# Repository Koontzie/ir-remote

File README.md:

# IR-Remote

**A three-button universal IR remote you program from your phone** — an ESP32-S3
blasts the infrared code, and a web page (no app store, no build step) tells it
which code to blast over Bluetooth.

The point is the last-mile problem in AV work: you're standing in front of an
unlabelled projector or a hotel TV with no remote, and you need power and input
switching *now*. This is a Flipper Zero's universal-remote trick, on $10 of parts,
in a form factor with real buttons you can hit without looking.

## Try it

**→ [koontzie.github.io/ir-remote/app/](https://koontzie.github.io/ir-remote/app/)**

The app is a single static HTML file with no dependencies and no backend. It talks
to the board with **Web Bluetooth**, which means:

- **Desktop Chrome / Edge / Android Chrome** — works as-is.
- **iOS: you need [Bluefy](https://apps.apple.com/us/app/bluefy-web-ble-browser/id1492822055).**
  Not a preference — **Safari has no Web Bluetooth support at all**, and every iOS
  browser is Safari underneath except the handful that ship their own BLE bridge.
  Bluefy is one of those. Open the link above inside Bluefy.
- **Firefox** — no Web Bluetooth. Won't work.

Without hardware you can still browse the code library; the connect button is the
only thing that needs a board.

## How it works

```
[phone or laptop browser]  ──Web Bluetooth──▶  [ESP32-S3 · BLE GATT]
                                                     │  writes to NVS (flash)
[3 physical buttons] ──GPIO──▶ [firmware] ──▶ [2N2222 ──▶ 2× IR LED] ──▶ device
```

Assign a code to a slot once, and the board **keeps it through a power cycle and
fires it with the browser completely disconnected.** It's a real remote, not a
Bluetooth accessory — the phone is a programming tool, not a dependency.

The code library ships in the repo: **317 brands, ~11,100 codes** across TVs,
projectors, monitors, AV receivers, soundbars, cable boxes, Blu-ray and DVD.
Search a brand, pick a function, assign it to a button. Codes shared across many
models of a brand are flagged as "blanket" codes and floated to the top, because
those are the ones most likely to just work.

**GATT interface** (device name `IR-Remote`):

| Role | UUID | Payload |
|---|---|---|
| service | `b457c32b-22b1-425f-8a88-4d6dc37ba4eb` | — |
| `config` (write) | `d997012d-7d2b-47de-ae87-bae14df446ef` | `{"slot":1,"proto":"SAMSUNG","code":"0xE0E040BF","bits":32}` |
| `trigger` (write) | `58397514-04a3-4265-9590-9d910c4e99d2` | `{"slot":1}` |
| `status` (notify) | `b8ddfe01-519f-430d-bd4e-aba0dd852e2c` | `saved:N` / `sent:N` / `pressed:N` / `err:…` |

Five slots (1–5); protocols NEC, SAMSUNG, SONY.

⚠️ **The GATT server is unauthenticated** — anyone in Bluetooth range can write a
config or trigger a slot. That's fine for bench use and it's a deliberate
trade-off, not an oversight; NimBLE bonding would close it if this ever left the
workbench.

## Where it stands

**It works.** The core is built and proven on the bench: IR transmit across a room
(20–30 ft), programming over Bluetooth from the app, codes persisting in flash
through a power cycle, all three physical buttons, and the searchable code library
end to end — pick a Samsung power code in the browser, assign it to a button, and
the TV across the room turns off.

It's a finished thing that does its job. What follows is the honest edge of it,
not a to-do list I'm apologising for.

- **USB-powered.** The circuit runs off the dev board's 5 V pin, so it needs a
  cable or a USB battery pack. A battery-and-deep-sleep version was started and
  stopped after it cost a dev board — see the postmortem below.
- **Identify mode is written but unproven.** Sweeping power codes until the device
  reacts, plus favourites, is implemented in the app and firmware but has never
  been run against real hardware.
- **The custom PCB is designed, not fabricated.** `hardware/` has a complete
  KiCad project, placed and partly routed. Nothing has been sent to a fab, so
  nothing about it is proven.
- **Bluetooth link drops occasionally** (`reason 520`, supervision timeout).
  Annoying, not dangerous — the stored codes and the IR output were verified
  correct either side of every drop.

The unit in the photos is currently dead, and it's a good story rather than a sad
one: during the battery experiment a cheap boost converter's solder-blob voltage
selector let go, silently jumped to 9 V, and cooked the dev board's regulator. The
design was never at fault, a socketed dev board makes it a two-minute swap, and
the full postmortem — along with every other fault this project hit — is in
[docs/DEVLOG.md](docs/DEVLOG.md).

## What's next

No timeline and no promises — the project does what it was built to do. If I pick
it back up:

- **An enclosure.** It's loose boards and panel-mount buttons right now. This is
  the one thing that would turn it from a working circuit into something you'd
  actually carry to a job.
- **Prove out identify mode** on a fresh dev board — the sweep is the feature that
  makes it genuinely universal rather than a nice code browser.
- **Polish the app UI.** It's functional and fast, but it's plainly a tool built
  by one person for one person.

## Bill of materials

| Qty | Part | Notes |
|---|---|---|
| 1 | **Seeed Studio XIAO ESP32-S3** dev board | Any ESP32-S3 dev board works; this is what's pictured. **Socket it** — dev boards die, and a socket makes that a pull instead of a desolder. |
| 2 | IR LED, 940 nm | Wired in series. Salvaged from a dead remote here. Verify a salvaged emitter is actually IR — it glows violet-white on a phone camera. |
| 1 | 2N2222 NPN transistor, TO-92 | Any general-purpose NPN with ≥150 mA collector current. |
| 1 | 33 Ω resistor | LED current limit — sets the ~100 mA pulse. |
| 1 | 1 kΩ resistor | Transistor base. |
| 1 | 470 µF electrolytic capacitor | Bulk decoupling across the 5 V rail. Steadies the rail during LED pulses. |
| 3 | R13-507 16 mm momentary buttons | Panel-mount, solder lugs, no polarity. Any momentary SPST works. |
| 1 | Protoboard + hookup wire | |

Roughly $10–15 if you're buying everything, less if you're raiding a parts bin.

## Wiring

Full card with health checks and measured values: **[hardware/WIRING.md](hardware/WIRING.md)**.

```
POWER
  Dev board 5V pin ──► 5V rail
  Dev board GND    ──► GND rail
  470µF cap across the rails: (+) → 5V, (−) stripe → GND, near the driver.

IR DRIVER (2N2222, TO-92)
  5V rail ──33Ω──► LED1 anode(+)
  LED1(−) ──► LED2(+)                 [series pair, both 940nm]
  LED2(−) ──► COLLECTOR
  EMITTER ──► GND rail
  GPIO4 ──1kΩ──► BASE (middle leg)

BUTTONS (INPUT_PULLUP, pressed = LOW)
  GPIO5 ──► button ──► GND   → slot 1
  GPIO2 ──► button ──► GND   → slot 2
  GPIO7 ──► button ──► GND   → slot 3
```

Two things that cost real bench time here, so they're worth repeating:

- **Meter the transistor's legs; don't assume them.** E/C order varies by vendor
  for the same part number. In diode mode with the red probe on Base, the outer
  leg with the *higher* forward drop is the Emitter.
- **A resistor being present on the board is not the same as it being in the
  current path.** The 33 Ω must be in series with the LEDs, not in the cap's
  branch. Check continuity to the right *node*.

## Build and flash

Toolchain (macOS, Homebrew) — these exact versions are what's verified:

| | Version |
|---|---|
| `arduino-cli` | 1.5.1 |
| `esp32` core | 3.3.10 |
| IRremoteESP8266 | 2.9.0 |
| NimBLE-Arduino | 2.5.0 |
| ArduinoJson | 7.4.3 |

```sh
arduino-cli core install esp32:esp32
arduino-cli lib install IRremoteESP8266 NimBLE-Arduino ArduinoJson

arduino-cli board list      # the port number is NOT stable across replugs
arduino-cli compile --fqbn esp32:esp32:esp32s3:CDCOnBoot=cdc firmware/remote_ble
arduino-cli upload -p <PORT> --fqbn esp32:esp32:esp32s3:CDCOnBoot=cdc firmware/remote_ble

sleep 20 | arduino-cli monitor -p <PORT> -c baudrate=115200
```

`CDCOnBoot=cdc` is required — the S3 talks over native USB CDC, and serial stays
silent without it. `arduino-cli monitor` exits instantly if stdin is closed, hence
the `sleep 20 |` when scripting it.

`firmware/phase1_ir_test/` is a deliberately minimal known-good IR sketch — it
sends one hard-coded Samsung code every 3 seconds. When something stops working,
flash that first to prove the LED path before suspecting anything else.

### Running the app locally

```sh
cd app && python3 -m http.server 8000
```

Open `http://localhost:8000` in desktop Chrome. `localhost` counts as a secure
context, so Web Bluetooth works without HTTPS.

## Repository layout

| Path | What |
|---|---|
| `firmware/remote_ble/` | The real firmware — BLE GATT + IR + 5 NVS-backed slots |
| `firmware/phase1_ir_test/` | Minimal known-good IR sketch, kept as a bisect tool |
| `app/index.html` | The whole app. One file, vanilla JS, no build step |
| `data/` | Generated IR code database — see [data/README.md](data/README.md) |
| `tools/flipper_ir_convert.py` | Flipper `.ir` → IRremoteESP8266 JSON converter + scraper |
| `hardware/` | KiCad 10 PCB project (unfabricated) + the wiring card |
| `docs/` | Design docs and the development log |
| `PLAN.md` | The plan |
| `docs/DEVLOG.md` | A running log of what actually happened — including the failures, in detail |

### Docs

[Code library + Identify mode design](docs/DESIGN-code-library.md) ·
[PCB design](hardware/DESIGN-pcb.md) ·
[hardware working notes](hardware/README.md) ·
[the IR database](data/README.md)

`docs/DEVLOG.md` is worth a look if you're building one of these. It's a blow-by-blow
of every fault hit along the way and how each was actually diagnosed — a dev board
bricked by a boost converter that silently drifted to 9 V, a transistor installed
E/C-reversed, a BLE advertisement overflowing 31 bytes so the device name was
silently dropped, and a board stuck in ROM download mode that looked exactly like
dead firmware. Each entry ends with the lesson rather than just the fix.

## Credits / data sources

The IR code database is built from
**[Lucaslhm/Flipper-IRDB](https://github.com/Lucaslhm/Flipper-IRDB)**, released
under **[CC0-1.0](https://creativecommons.org/publicdomain/zero/1.0/)** — a public
domain dedication that asks nothing of anyone reusing it. It's credited here
anyway, because a community-maintained database of 300+ brands is a real piece of
work and saying so is good manners. See [data/README.md](data/README.md) for how
it's converted and regenerated.

The firmware stands on
[IRremoteESP8266](https://github.com/crankyoldgit/IRremoteESP8266) (despite the
name, first-class ESP32 support) and
[NimBLE-Arduino](https://github.com/h2zero/NimBLE-Arduino).

> **A note on history:** until 2026-07-31 this repo also contained two universal
> code lists taken from
> [DarkFlippers/unleashed-firmware](https://github.com/DarkFlippers/unleashed-firmware),
> which is **GPL-3.0**. Those files and everything derived from them were removed
> when the project adopted the MIT license, and the sweep lists were rebuilt from
> the CC0 database instead. **They are still present in earlier commits** — git
> history was not rewritten. Nothing in the current tree derives from them.

## License

[MIT](LICENSE) © 2026 Tyler Koontz.

## Support

If you found this useful, you can [buy me a coffee](https://ko-fi.com/tylerxkoontz).

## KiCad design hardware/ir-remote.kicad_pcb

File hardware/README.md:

# hardware/ — BLE IR remote PCB

KiCad 10 project for the custom board. Design decisions and rationale live in
[DESIGN-pcb.md](DESIGN-pcb.md); this file is the how-to-work-on-it notes.

**Nothing here has been fabricated. Nothing is proven.**

| File | What it is |
|---|---|
| `ir-remote.kicad_sch` | Schematic — flat sheet, zoned power / MCU / USB / IR / inputs |
| `ir-remote.kicad_pcb` | Board — 2-layer, 30 × 58mm |
| `ir-remote.kicad_pro` | Project + net classes (POWER_IR, POWER_3V3, USB_DIFF) |
| `DESIGN-pcb.md` | Pin map, power tree, BOM, sleep budget, decisions |

---

## ⚠️ KiCad 10 net format — do not "repair" it

KiCad 10 (board format `20260206`) references nets **by name**:

```
(net "GND")        <- pads, tracks and vias, KiCad 10
(net 2 "GND")      <- KiCad <= 9 pads; the numeric index and the top-level
                      (net N "name") table no longer exist
```

`kicad-cli --save-board` — KiCad's own serialiser — writes the name-only form,
and DRC resolves it correctly (`Pad 5 [BTN1]`, `Track [BTN1]`). The kicad-mcp
writer produces the same thing, correctly.

**This tripped me once.** `grep '(net [0-9]'` returns zero on a perfectly healthy
KiCad 10 board, which looks alarming. I concluded the MCP was corrupting the
file and wrote a script to add the old index table back. It "worked" only
because KiCad still parses the legacy form — the board was never broken, and the
script eventually introduced a genuine inconsistency of its own. Deleted.

**Check what this KiCad version actually writes before concluding a tool is
broken:**

```sh
kicad-cli pcb drc --output /tmp/drc.rpt ir-remote.kicad_pcb
grep -A3 unconnected /tmp/drc.rpt     # healthy: nets show as [GND], [BTN1], ...
```

## Real MCP traps that do apply

- **External edits block the next auto-save.** Touch the `.kicad_pcb` outside the
  MCP and its next save is *refused* (mtime guard, `diskChangedExternally`);
  your changes then exist only in server memory until they're lost. Call
  `open_project` to re-sync first.
- **`assign_net_to_class` and `add_net_class` are advertised but not
  implemented** — they return `Unknown command`. Net-class assignment has to be
  written into `ir-remote.kicad_pro` (`net_settings.netclass_patterns`) directly.
- **`refill_zones` has a documented segfault risk** on the swig backend. Use
  `kicad-cli pcb drc --refill-zones --save-board` instead — it fills zones
  natively and safely.
- **ERC violation coordinates from the MCP are in unusable normalised units.**
  Use `kicad-cli sch erc` for a readable report.

---

## Verification commands

```sh
# ERC
kicad-cli sch erc --output erc.rpt --severity-all ir-remote.kicad_sch

# DRC, refilling zones first (DRC on unfilled pours is meaningless)
kicad-cli pcb drc --refill-zones --save-board --output drc.rpt --severity-error ir-remote.kicad_pcb

# 3D renders
kicad-cli pcb render --output layout-top.png    --side top    ir-remote.kicad_pcb
kicad-cli pcb render --output layout-bottom.png --side bottom ir-remote.kicad_pcb
```

## Autorouting

Freerouting, not the MCP's `autoroute` (it probes `/usr/bin/java`, the macOS
stub, and will not find a Homebrew JDK).

- **Freerouting 2.2.x needs Java 25** (class file v69). **Use 2.1.0** — class
  file v65, runs on Java 21.
- Java: `/opt/homebrew/opt/openjdk@21/bin/java` (keg-only, not on PATH).

```sh
java -Djava.awt.headless=true -jar ~/.kicad-mcp/freerouting.jar \
     -de ir-remote.dsn -do ir-remote.ses -mp 50 -dct 0
```

**The MCP DSN export drops net classes** — everything comes out at 0.2mm,
including the 220mA IR paths. The DSN must be patched to add `POWER_IR` (600µm),
`POWER_3V3` (500µm) and `USB_DIFF` (250µm) classes before routing.

## Fab notes (JLCPCB, 2-layer)

| Parameter | Value |
|---|---|
| Size | 30 × 58mm, 2mm corner radius |
| Layers / thickness | 2 / 1.6mm |
| Surface finish | HASL (lead-free fine) |
| Min track / clearance | 0.127mm / 0.2mm |
| Min drill | 0.3mm |
| Copper | 1oz |

**Watch item:** the stock KiCad `ESP32-S3-WROOM-1` footprint ships 12 thermal
vias at **0.2mm drill**, under JLCPCB's 0.3mm minimum. They are enlarged to
0.3mm in this board. If the footprint is ever re-imported from the library,
that fix is lost — re-check before ordering.

## Antenna keepout — do not "optimise" this away

The ESP32-S3-WROOM-1 footprint declares a large antenna clearance area
(x < 7.75mm for the full board height in the current orientation). No copper,
no pour, no components, no stitching vias in it. The ground pours are cut back
to respect it, which is why the left strip of the board looks empty.

The MCP's `add_gnd_stitching_vias` works off the **board outline, not the pour
outline**, and will happily place vias straight through the keepout. Use the
`in_zones` strategy or place them by hand.

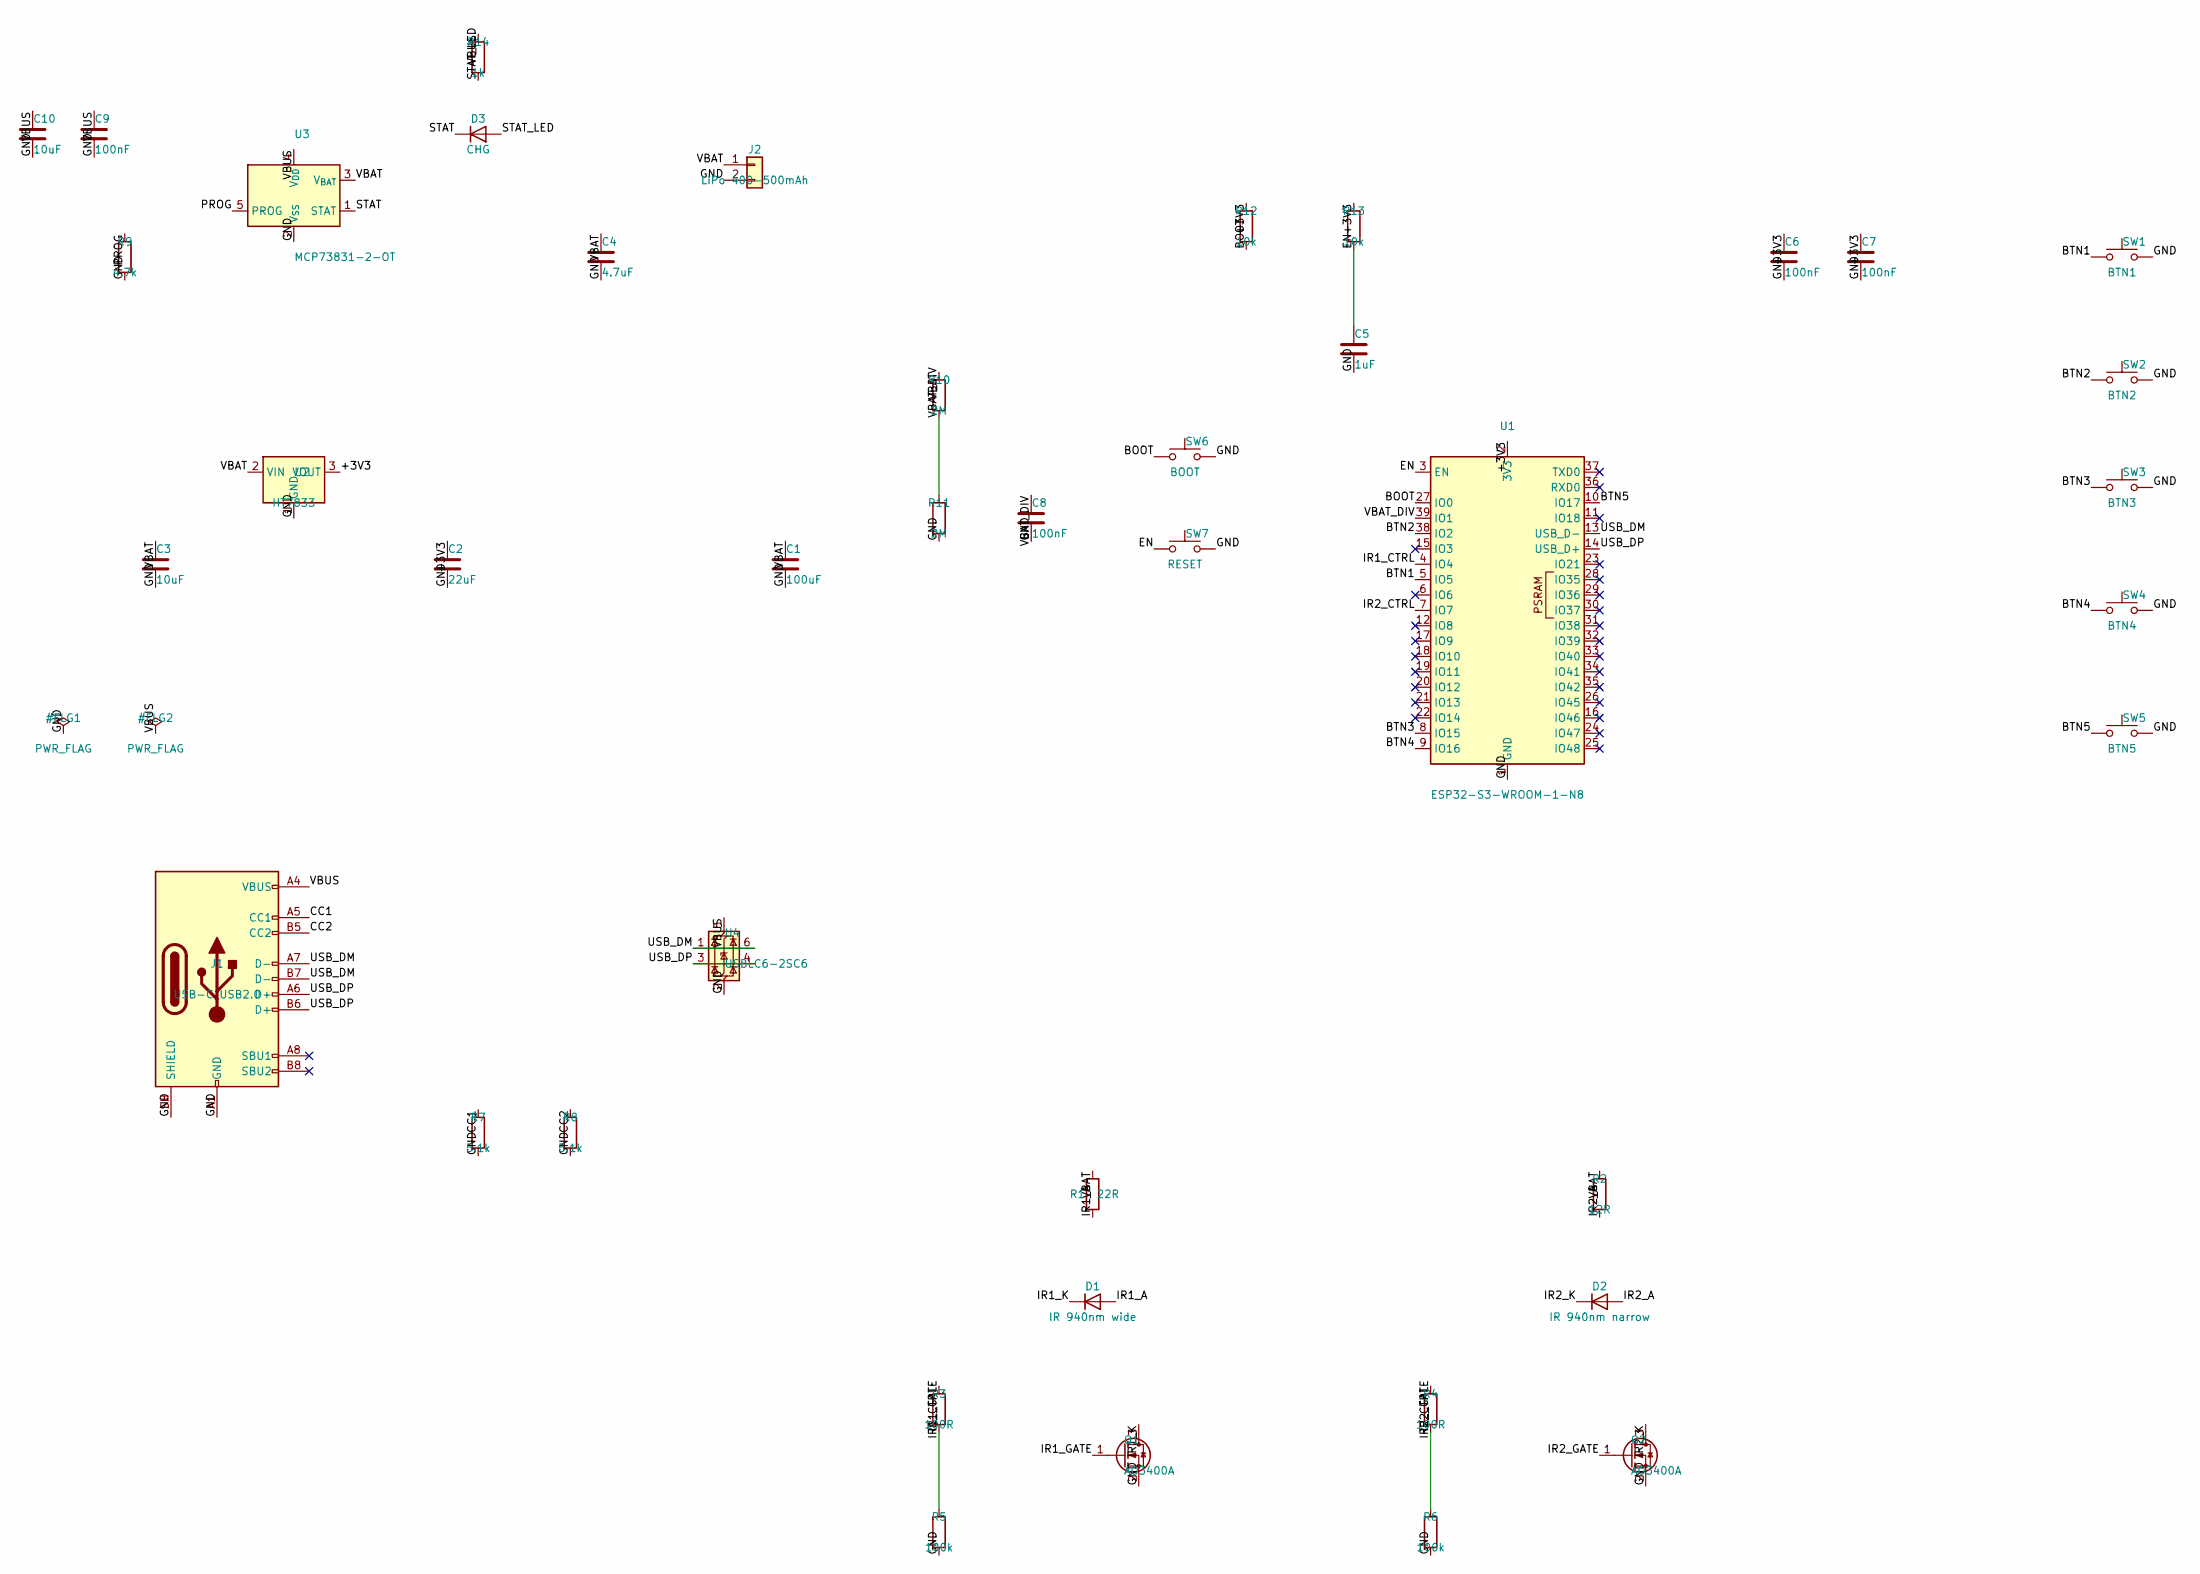
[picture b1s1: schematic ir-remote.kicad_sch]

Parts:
C1: 100uF; C_1210_3225Metric
C2: 22uF; C_0805_2012Metric_Pad1.18x1.45mm_HandSolder
C3, C10: 10uF; C_0603_1608Metric_Pad1.08x0.95mm_HandSolder
C4: 4.7uF; C_0603_1608Metric_Pad1.08x0.95mm_HandSolder
C5: 1uF; C_0603_1608Metric_Pad1.08x0.95mm_HandSolder
C6, C7, C8, C9: 100nF; C_0603_1608Metric_Pad1.08x0.95mm_HandSolder
D1: IR 940nm wide; LED_D5.0mm
D2: IR 940nm narrow; LED_D5.0mm
D3: CHG; LED_0603_1608Metric
J1: USB-C USB2.0; USB_C_Receptacle_HRO_TYPE-C-31-M-12
J2: LiPo 400-500mAh; JST_PH_S2B-PH-K_1x02_P2.00mm_Horizontal
Q1, Q2: AO3400A; SOT-23
R1: 22R; R_0603_1608Metric_Pad0.98x0.95mm_HandSolder
R2: 12R; R_0603_1608Metric_Pad0.98x0.95mm_HandSolder
R3, R4: 100R; R_0603_1608Metric_Pad0.98x0.95mm_HandSolder
R5, R6: 100k; R_0603_1608Metric_Pad0.98x0.95mm_HandSolder
R7, R8: 5.1k; R_0603_1608Metric_Pad0.98x0.95mm_HandSolder
R9: 4.7k; R_0603_1608Metric_Pad0.98x0.95mm_HandSolder
R10, R11: 2M; R_0603_1608Metric_Pad0.98x0.95mm_HandSolder
R12, R13: 10k; R_0603_1608Metric_Pad0.98x0.95mm_HandSolder
R14: 1k; R_0603_1608Metric_Pad0.98x0.95mm_HandSolder
SW1: BTN1; SW_SPST_SKQG_WithStem
SW2: BTN2; SW_SPST_SKQG_WithStem
SW3: BTN3; SW_SPST_SKQG_WithStem
SW4: BTN4; SW_SPST_SKQG_WithStem
SW5: BTN5; SW_SPST_SKQG_WithStem
SW6: BOOT; SW_SPST_SKQG_WithStem
SW7: RESET; SW_SPST_SKQG_WithStem
U1: ESP32-S3-WROOM-1-N8; ESP32-S3-WROOM-1
U2: HT7833; SOT-89-3
U3: MCP73831-2-OT; SOT-23-5
U4: USBLC6-2SC6; SOT-23-6

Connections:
+3V3: C2.1, C6.1, C7.1, R12.1, R13.1, U1.2 (3V3), U2.3 (VOUT)
BOOT: R12.2, SW6.1, U1.27 (IO0)
BTN1: SW1.1, U1.5 (IO5)
BTN2: SW2.1, U1.38 (IO2)
BTN3: SW3.1, U1.8 (IO15)
BTN4: SW4.1, U1.9 (IO16)
BTN5: SW5.1, U1.10 (IO17)
CC1: J1.A5 (CC1), R7.1
CC2: J1.B5 (CC2), R8.1
EN: C5.1, R13.2, SW7.1, U1.3 (EN)
GND: C1.2, C2.2, C3.2, C4.2, C5.2, C6.2, C7.2, C8.2, C9.2, C10.2, J1.A1 (GND), J1.A12 (GND), J1.B1 (GND), J1.B12 (GND), J1.SH (SHIELD), J2.2, Q1.2 (S), Q2.2 (S), R5.2, R6.2, R7.2, R8.2, R9.2, R11.2, SW1.2, SW2.2, SW3.2, SW4.2, SW5.2, SW6.2, SW7.2, U1.1 (GND), U1.40 (GND), U1.41 (GND), U2.1 (GND), U3.2 (V_{SS}), U4.2 (GND)
IR1_A: D1.2 (A), R1.2
IR1_CTRL: R3.1, U1.4 (IO4)
IR1_GATE: Q1.1 (G), R3.2, R5.1
IR1_K: D1.1 (K), Q1.3 (D)
IR2_A: D2.2 (A), R2.2
IR2_CTRL: R4.1, U1.7 (IO7)
IR2_GATE: Q2.1 (G), R4.2, R6.1
IR2_K: D2.1 (K), Q2.3 (D)
PROG: R9.1, U3.5 (PROG)
STAT: D3.1 (K), U3.1 (STAT)
STAT_LED: D3.2 (A), R14.2
USB_DM: J1.A7 (D-), J1.B7 (D-), U1.13 (USB_D-), U4.1 (I/O1), U4.6 (I/O1)
USB_DP: J1.A6 (D+), J1.B6 (D+), U1.14 (USB_D+), U4.3 (I/O2), U4.4 (I/O2)
VBAT: C1.1, C3.1, C4.1, J2.1, R1.1, R2.1, R10.1, U2.2 (VIN), U3.3 (V_{BAT})
VBAT_DIV: C8.1, R10.2, R11.1, U1.39 (IO1)
VBUS: C9.1, C10.1, J1.A4 (VBUS), J1.A9 (VBUS), J1.B4 (VBUS), J1.B9 (VBUS), R14.1, U3.4 (V_{DD}), U4.5 (VBUS)

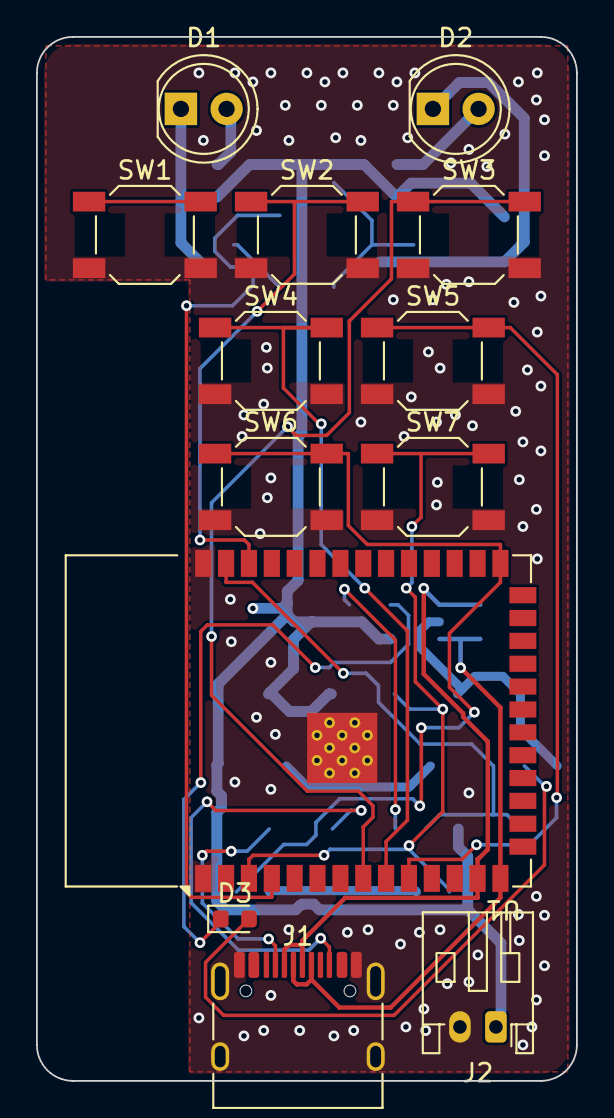
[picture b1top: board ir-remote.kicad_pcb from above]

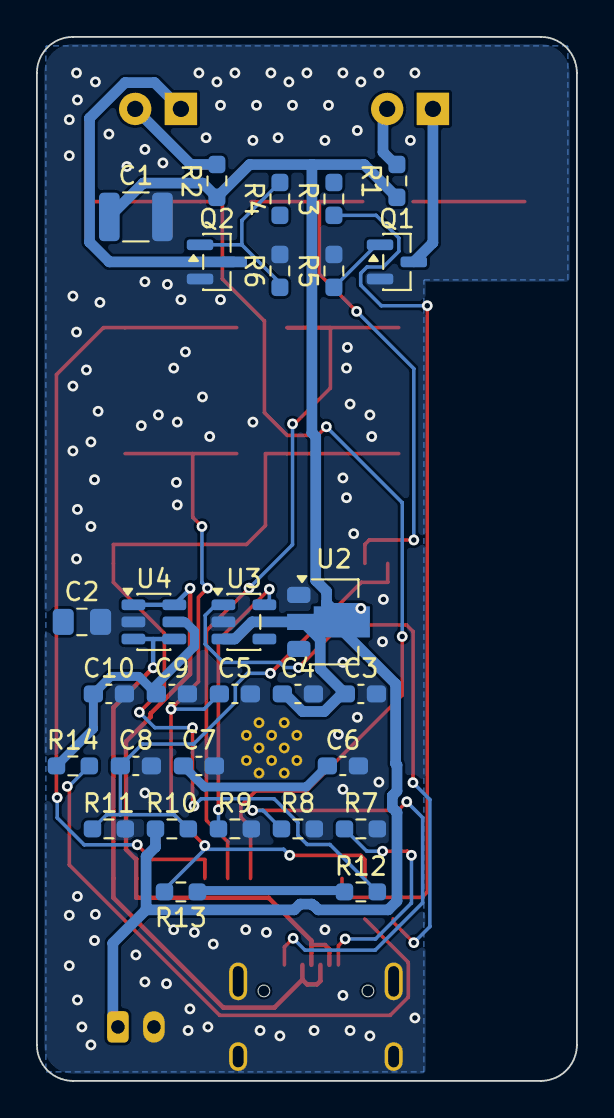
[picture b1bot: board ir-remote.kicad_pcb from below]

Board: 2 copper layers, 30.0 x 58.0 mm, 42 parts (29 on the bottom side), 27 nets.
